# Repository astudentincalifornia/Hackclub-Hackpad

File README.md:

# SquarePad

The **SquarePad** is a custom macropad with 8 switches with backlight LEDs, a rotary encoder, and an OLED screen. The **SquarePad** is a useful tool for custom shortcuts and a knob to manipulate any adjustable parameters for ease of use in different software.
## BOM
- 8x Cherry MX Switches
- 1x Seeed XIAO RP2040
- 1x 0.91in 128x32px OLED
- 1x EC11 Encoder
- 1x 3D printed Top
- 1x 3D printed Bottom
- 4x M3x16mm Screw
- 4x M3x5mx4mm heatset inserts
- 8x SK6812 MINI-E LEDs
- 9x Through-hole 1N4148 Diodes

## Features
- **8 Different Back Light Switches** for me to customize
- **A Rotary Encoder Switch** for me to customize ~~right now set to remove permission from all my files~~ for useful tool or shortcuts
- **Oled Screen** for me to gain maximum stimulation while working
## Story
I planned to make a macro pad for me to use different macros but after some research,I hoped to be able to use the various macros for software such as cadding or automating some processes ~~that literrally just takes a couple seconds~~.
The Case took the most time to complete as I was afraid that the dimensions won't be right and might not be able to fit everything I had on my PCB
The PCB and Schematic took some time as I did some research and ~~copied~~ had some inspiration from others.
The firmware took the least time as I already had prior coding experience.
## PCB

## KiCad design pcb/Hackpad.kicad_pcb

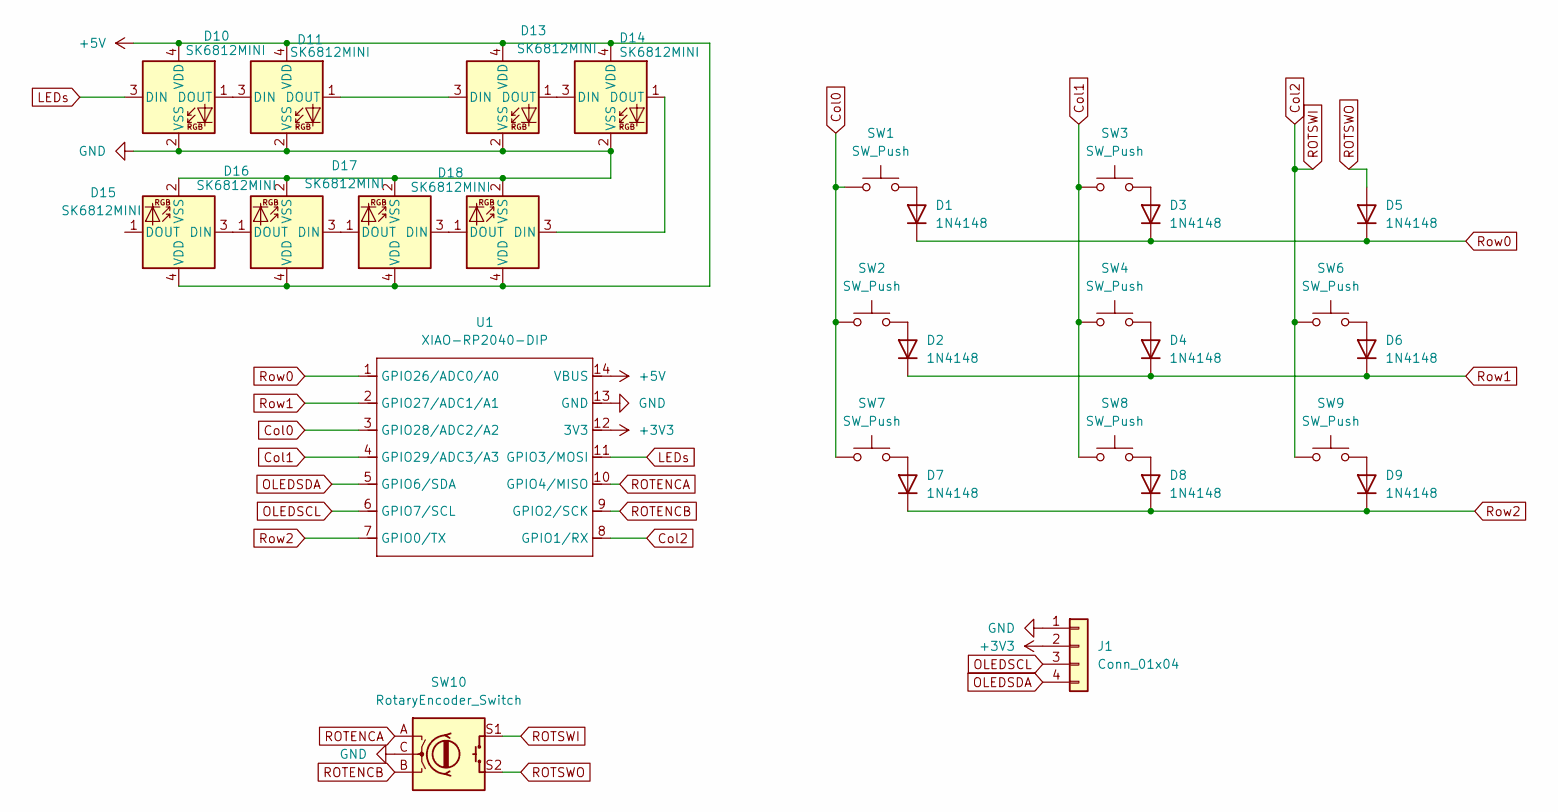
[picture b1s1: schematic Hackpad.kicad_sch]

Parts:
D1, D2, D3, D4, D5, D6, D7, D8, D9: 1N4148; D_DO-35_SOD27_P7.62mm_Horizontal
D10, D11, D13, D14, D15, D16, D17, D18: SK6812MINI; SK6812-MINI-E
J1: Conn_01x04; SSD1306-0.91-OLED-4pin-128x32
SW1, SW2, SW3, SW4, SW6, SW7, SW8, SW9: SW_Push; SW_Cherry_MX_1.00u_PCB_3d
SW10: RotaryEncoder_Switch; RotaryEncoder_Alps_EC12E-Switch_Vertical_H20mm
U1: XIAO-RP2040-DIP

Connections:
+3V3: J1.2, U1.12 (3V3)
+5V: D10.4 (VDD), D11.4 (VDD), D13.4 (VDD), D14.4 (VDD), D15.4 (VDD), D16.4 (VDD), D17.4 (VDD), D18.4 (VDD), U1.14 (VBUS)
Col0: SW1.1, SW2.1, SW7.1, U1.3 (GPIO28/ADC2/A2)
Col1: SW3.1, SW4.1, SW8.1, U1.4 (GPIO29/ADC3/A3)
Col2: SW6.1, SW9.1, SW10.S1, U1.8 (GPIO1/RX)
GND: D10.2 (VSS), D11.2 (VSS), D13.2 (VSS), D14.2 (VSS), D15.2 (VSS), D16.2 (VSS), D17.2 (VSS), D18.2 (VSS), J1.1, SW10.C, U1.13 (GND)
LEDs: D10.3 (DIN), U1.11 (GPIO3/MOSI)
unnamed: D1.2 (A), SW1.2
unnamed: D2.2 (A), SW2.2
unnamed: D3.2 (A), SW3.2
unnamed: D4.2 (A), SW4.2
unnamed: D6.2 (A), SW6.2
unnamed: D7.2 (A), SW7.2
unnamed: D8.2 (A), SW8.2
unnamed: D9.2 (A), SW9.2
unnamed: D10.1 (DOUT), D11.3 (DIN)
unnamed: D11.1 (DOUT), D13.3 (DIN)
unnamed: D13.1 (DOUT), D14.3 (DIN)
unnamed: D14.1 (DOUT), D18.3 (DIN)
unnamed: D15.3 (DIN), D16.1 (DOUT)
unnamed: D16.3 (DIN), D17.1 (DOUT)
unnamed: D17.3 (DIN), D18.1 (DOUT)
OLEDSCL: J1.3, U1.6 (GPIO7/SCL)
OLEDSDA: J1.4, U1.5 (GPIO6/SDA)
ROTENCA: SW10.A, U1.10 (GPIO4/MISO)
ROTENCB: SW10.B, U1.9 (GPIO2/SCK)
ROTSWO: D5.2 (A), SW10.S2
Row0: D1.1 (K), D3.1 (K), D5.1 (K), U1.1 (GPIO26/ADC0/A0)
Row1: D2.1 (K), D4.1 (K), D6.1 (K), U1.2 (GPIO27/ADC1/A1)
Row2: D7.1 (K), D8.1 (K), D9.1 (K), U1.7 (GPIO0/TX)

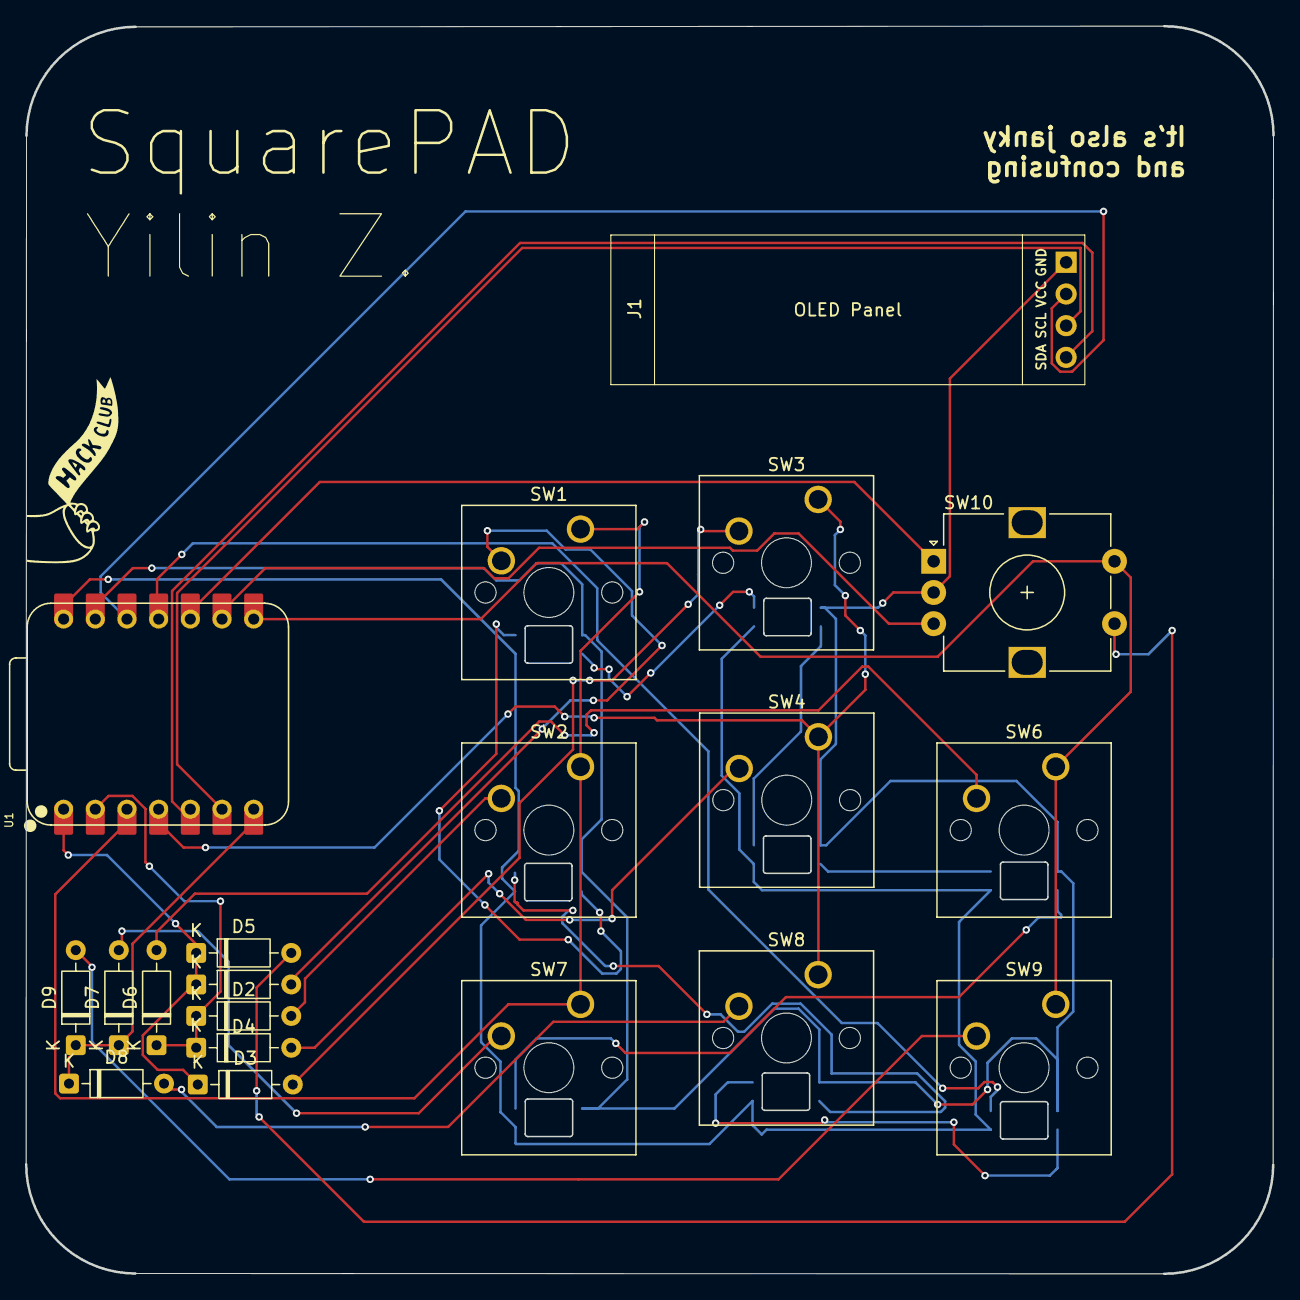
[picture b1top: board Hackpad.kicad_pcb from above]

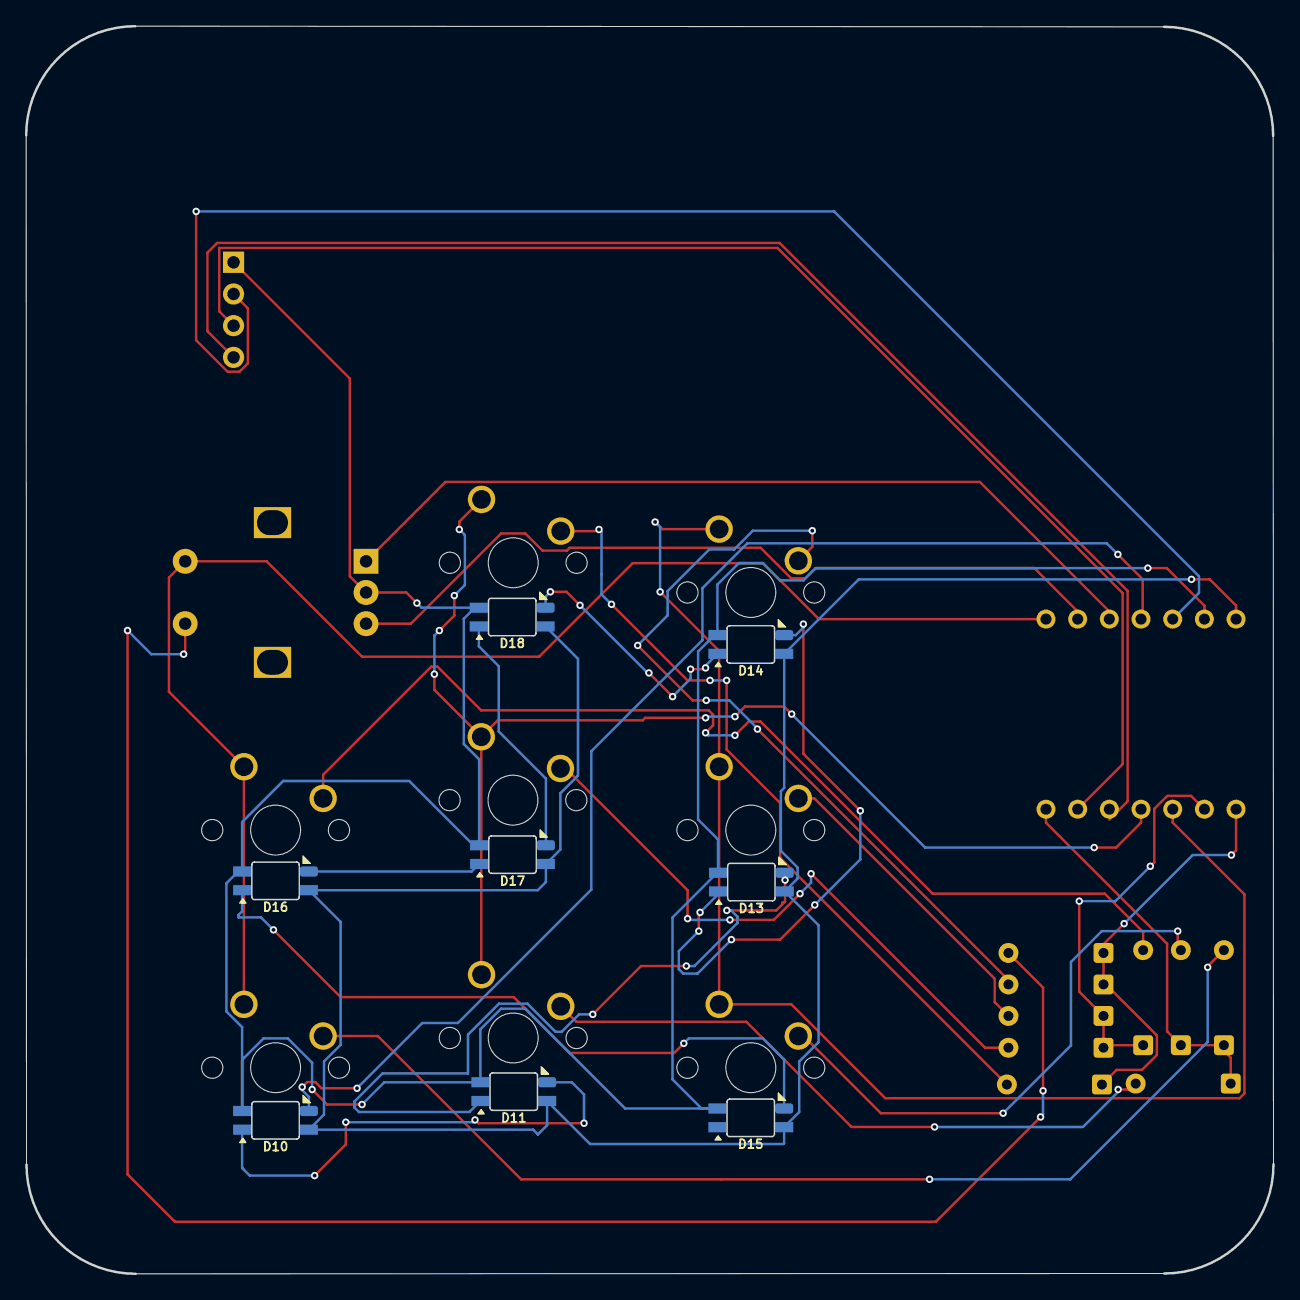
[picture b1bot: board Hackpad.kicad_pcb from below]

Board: 2 copper layers, 100.0 x 100.0 mm, 28 parts (8 on the bottom side), 30 nets.

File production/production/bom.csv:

Designator,Footprint,Quantity,Value,LCSC Part #
"D1, D2, D3, D4, D5, D6, D7, D8, D9",D_DO-35_SOD27_P7.62mm_Horizontal,9,1N4148,
"D10, D11, D13, D14, D15, D16, D17, D18",SK6812-MINI-E,8,SK6812MINI,
J1,SSD1306-0.91-OLED-4pin-128x32,1,Conn_01x04,
"SW1, SW2, SW3, SW4, SW6, SW7, SW8, SW9",SW_Cherry_MX_1.00u_PCB_3d,8,SW_Push,
SW10,RotaryEncoder_Alps_EC12E-Switch_Vertical_H20mm,1,RotaryEncoder_Switch,
U1,XIAO-RP2040-DIP,1,XIAO-RP2040-DIP,

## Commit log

2025-07-06 Create s
2025-07-08 Rename Screenshot 2025-07-08 103243.png to FullCase.png
2025-07-08 Rename Screenshot 2025-07-08 103306.png to Case1.png
